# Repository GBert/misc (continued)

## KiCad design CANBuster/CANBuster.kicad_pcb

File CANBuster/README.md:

# MäCAN-Project

 by [Gerhard Bertelsmann](mailto:info@gerhard-bertelsmann.de) 

Hier entsteht ein System zur digitalen Steuerung einer Modellbahn, das auf dem CAN-Bus-Protokoll von Märklin basiert. Ziel ist es, eine preisgünstige und frei zugängliche Lösung zu schaffen.

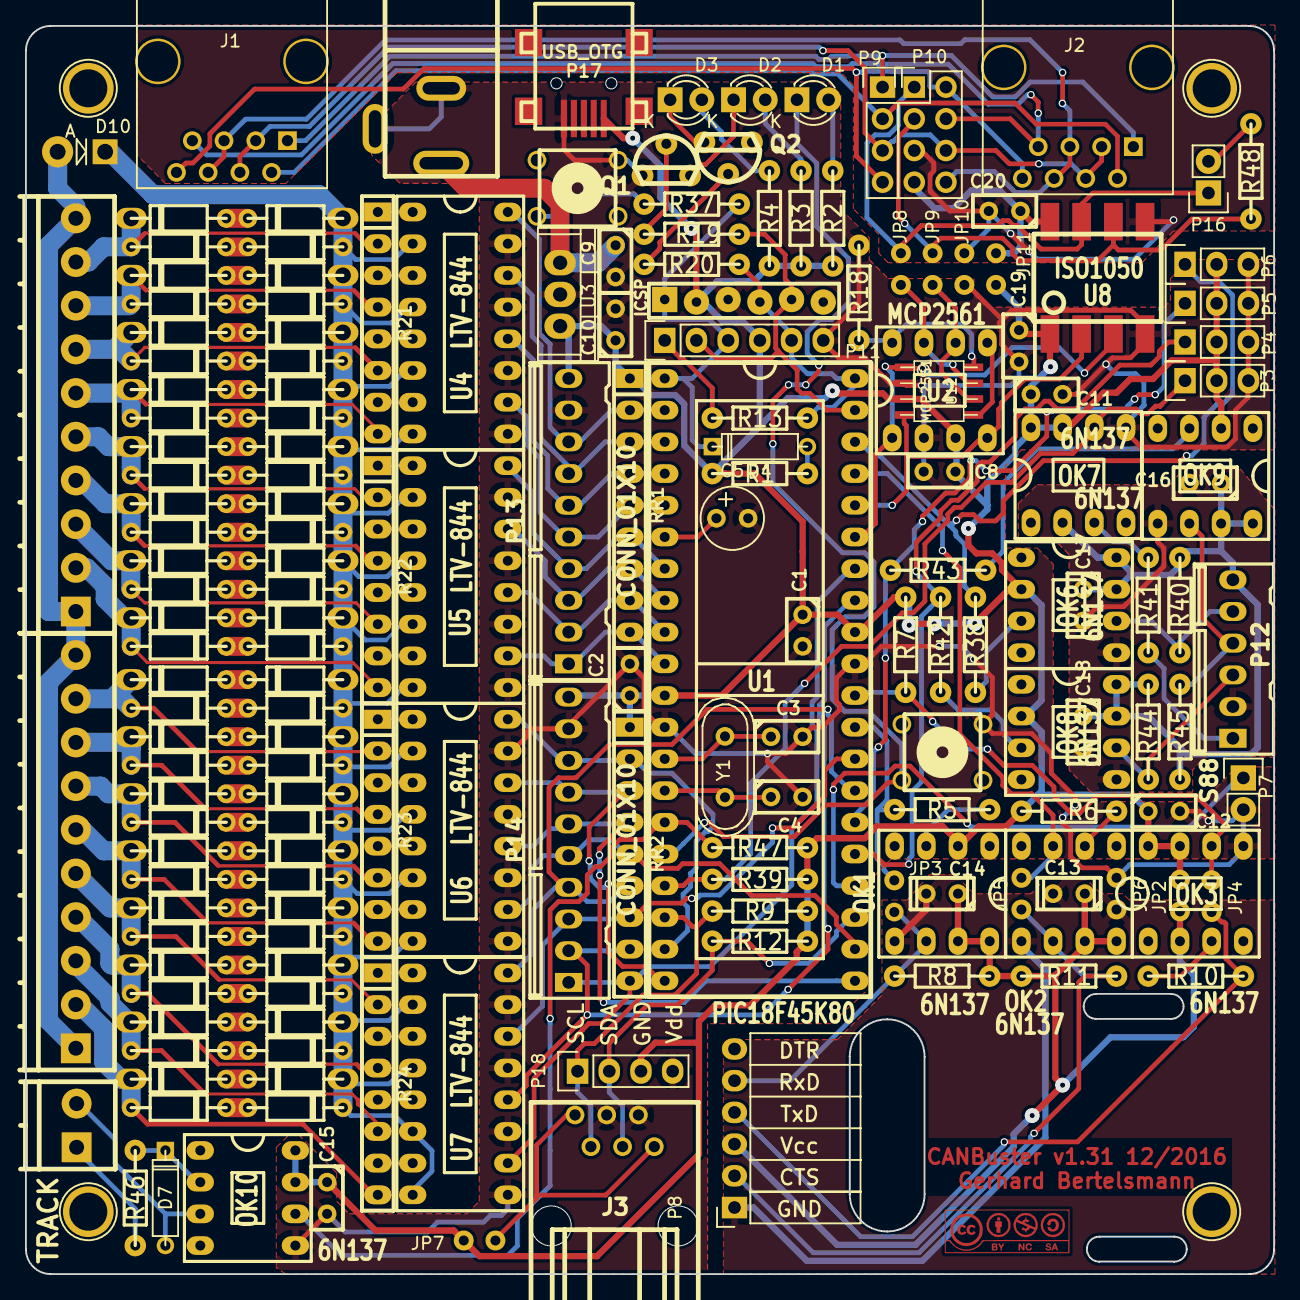
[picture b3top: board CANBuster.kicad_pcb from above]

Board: 2 copper layers, 100.0 x 100.0 mm, 177 parts (0 on the bottom side), 152 nets.

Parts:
C1, C2, C8, C9, C10, C11, C12, C13, C14, C15, C16, C17, C18, C19, C20: 100nF; cnp_3mm_disc
C3, C4: 22pf; cnp_3mm_disc
C5: 47uF; Elko_vert_11x5mm_RM2.5
CON1: BARREL_JACK; dc_socket
D1, D2, D3: LED; LED-3MM
D4: BAT43; D3
D7: 1N4148; D3
D10: D; Diode_DO-41_SOD81_Vertical_AnodeUp
D11, D12, D13, D14, D21, D22, D23, D24, D31, D32, D33, D34, D41, D42, D43, D44, D51, D52, D53, D54, D61, D62, D63, D64, D71, D72, D73, D74, D81, D82, D83, D84, D91, D92, D93, D94, D101, D102, D103, D104, D111, D112, D113, D114, D121, D122, D123, D124, D131, D132, D133, D134, D141, D142, D143, D144, D151, D152, D153, D154, D161, D162, D163, D164: D; diode_do35
J1, J2: RJ45; RJ45_8
J3: RJ12; molex_6p6c
JP1: ICSP
JP2, JP3, JP4, JP5, JP6, JP7, JP8, JP9, JP10, JP11: JUMPER; SolderWirePad_2x_0-2.54mmDrill
OK1, OK2, OK3, OK6, OK7, OK8, OK9, OK10: 6N137; dil_8-300_socket
P1, P2: CONN_01X10; pt_1,5-10-3,5-h
P3, P4, P5, P6: CONN_01X03; Pin_Header_Straight_1x03
P7, P16: CONN_01X02; Pin_Header_Straight_1x02
P8: CONN_01X06; Socket_Strip_Angled_1x06
P9, P18: CONN_01X04; Pin_Header_Straight_1x04
P10: CONN_02X04; Pin_Header_Straight_2x04
P11: RS232-Programmer; Socket_Strip_Straight_1x06
P12: S88; kk100_22-23-2061
P13, P14: CONN_01X10; kk100_22-23-2101
P15: TRACK; pt_1,5-2-3,5-h
P17: USB_OTG; conn_usb_B_mini_smd
Q1, Q2: BC547; to92_3
R1: 4k7; RC03
R2, R3, R4: 1,5k; RC03
R5, R6, R38, R41, R43, R47: 390; RC03
R7, R13, R39, R40, R44, R45: 1K; RC03
R8, R11: 1k; RC03
R9, R12: 3k3; RC03
R10: 270; RC03
R18, R19, R20: 10k; RC03
R21, R22, R23, R24: R-SIL_8NB; r-sil_8
R37: 470; RC03
R42: 330; RC03
R46: 1k5; RC03
R48: 120; RC03
RR1, RR2: RR8; r-sil_9
SW1, SW2: SW_PUSH; PCB_PUSH
U1: PIC18F45K80; dil_40-600_socket
U2: MCP2561; dil_8-300_socket
U3: 7805; TO-220
U4, U5, U6, U7: LTV-844; dil_16-300_socket
U8: ISO1050; mdip_8
U12: MCP2561; so-8
Y1: 16MHz; Crystal_HC49-U_Vertical

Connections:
+5V: C20.1, JP11.2, P10.7, U8.8
/CANH: JP8.2, P10.1, P16.1, U8.7
/CANL: JP9.2, P10.3, R48.1, U8.6
/CANRX: U1.36, U2.4, U8.2, U12.4
/CANTX: U1.35, U2.1, U8.3, U12.1
/CTS: JP5.1, OK2.3, U1.37
/IO1: P13.8, RR1.2, U1.2, U4.16
/IO2: P13.7, RR1.3, U1.3, U4.14
/IO3: P13.6, RR1.4, U1.4, U4.12
/IO4: P13.5, RR1.5, U1.5, U4.10
/IO5: P13.4, RR1.6, U1.7, U5.16
/IO6: P13.3, RR1.7, U1.8, U5.14
/IO7: P13.2, RR1.8, U1.9, U5.12
/IO8: P13.1, RR1.9, U1.10, U5.10
/IO9: P14.8, RR2.2, U1.19, U6.16
/IO10: P14.7, RR2.3, U1.20, U6.14
/IO11: P14.6, RR2.4, U1.21, U6.12
/IO12: P14.5, RR2.5, U1.22, U6.10
/IO13: P14.4, RR2.6, U1.27, U7.16
/IO14: P14.3, RR2.7, U1.28, U7.14
/IO15: P14.2, RR2.8, U1.33, U7.12
/IO16: P14.1, RR2.9, U1.34, U7.10
/PGC: JP1.5, P11.2, R19.2, U1.39
/PGD: JP1.4, P11.5, R13.1, R20.2, U1.40
/PGD_IN: P11.1, R13.2
/PWM1: OK7.6, P3.1, R39.1, U1.17
/PWM2: P4.1, R42.2, U1.25
/PWM3: P5.1, R43.2, U1.26
/PWM4: P6.1, R38.2, U1.38
/RxD: JP4.1, OK3.6, R7.1, U1.30
/S88_CLOCK: OK8.6, P12.3, R44.1
/S88_DATA: P12.1, R41.1
/S88_LOAD: OK9.6, P12.4, R45.1
/S88_RESET: OK6.6, P12.5, R40.1
/SCL: J3.2, P18.1, R9.1, U1.18
/SDA: J3.4, P18.2, R12.1, U1.23
/SNIFF: OK10.6, R47.1, U1.15
/STATUS: D1.1, SW2.2, U1.16
/TxD: JP3.1, R5.2, U1.29
/_CTS: JP5.2, OK2.6, P8.2, R11.2
/_RxD: JP3.2, OK1.6, P8.5, R8.1
/_TxD: JP4.2, P8.4, R10.1
/~MCLR: D4.1, JP1.1, P11.3, R37.1, U1.1
GND: C1.2, C2.2, C3.2, C4.2, C5.2, C8.2, C9.2, C10.2, C11.2, C12.2, C15.2, C19.2, CON1.1, CON1.2, J3.3, J3.5, JP1.3, JP6.1, JP10.1, OK3.5, OK7.5, OK10.5, P3.3, P4.3, P5.3, P6.3, P7.2, P11.6, P13.9, P14.9, P17.5, P18.4, Q1.3, Q2.3, R18.1, SW1.1, SW2.1, U1.12, U1.31, U2.2, U3.GND, U4.9, U4.11, U4.13, U4.15, U5.9, U5.11, U5.13, U5.15, U6.9, U6.11, U6.13, U6.15, U7.9, U7.11, U7.13, U7.15, U8.4, U12.2
GNDA: C16.2, C17.2, C18.2, OK6.5, OK8.5, OK9.5, P12.2
GNDD: C20.2, JP10.2, P10.5, U8.5
unnamed: C3.1, U1.13, Y1.1
unnamed: C4.1, U1.14, Y1.2
unnamed: C5.1, U1.6
unnamed: C9.1, CON1.3, U3.VI
unnamed: D1.2, R2.2
unnamed: D2.1, Q1.1
unnamed: D2.2, R3.2
unnamed: D3.1, Q2.1
unnamed: D3.2, R4.2
unnamed: D4.2, R1.2
unnamed: D7.1, OK10.2, R46.1
unnamed: D7.2, OK10.3, P15.2
unnamed: D10.1, D12.1, D14.2, D22.1, D24.2, D32.1, D34.2, D42.1, D44.2, D52.1, D54.2, D62.1, D64.2, D72.1, D74.2, D82.1, D84.2, D92.1, D94.2, D102.1, D104.2, D112.1, D114.2, D122.1, D124.2, D132.1, D134.2, D142.1, D144.2, D152.1, D154.2, D162.1, D164.2, U4.2, U4.4, U4.6, U4.8, U5.2, U5.4, U5.6, U5.8, U6.2, U6.4, U6.6, U6.8, U7.2, U7.4, U7.6, U7.8
unnamed: D10.2, P1.1, P1.10, P2.1, P2.10
unnamed: D11.1, D12.2
unnamed: D11.2, D13.1, P2.9, R21.2
unnamed: D13.2, D14.1
unnamed: D21.1, D22.2
unnamed: D21.2, D23.1, P2.8, R21.4
unnamed: D23.2, D24.1
unnamed: D31.1, D32.2
unnamed: D31.2, D33.1, P2.7, R21.6
unnamed: D33.2, D34.1
unnamed: D41.1, D42.2
unnamed: D41.2, D43.1, P2.6, R21.8
unnamed: D43.2, D44.1
unnamed: D51.1, D52.2
unnamed: D51.2, D53.1, P2.5, R22.2
unnamed: D53.2, D54.1
unnamed: D61.1, D62.2
unnamed: D61.2, D63.1, P2.4, R22.4
unnamed: D63.2, D64.1
unnamed: D71.1, D72.2
unnamed: D71.2, D73.1, P2.3, R22.6
unnamed: D73.2, D74.1
unnamed: D81.1, D82.2
unnamed: D81.2, D83.1, P2.2, R22.8
unnamed: D83.2, D84.1
unnamed: D91.1, D92.2
unnamed: D91.2, D93.1, P1.9, R23.2
unnamed: D93.2, D94.1
unnamed: D101.1, D102.2
unnamed: D101.2, D103.1, P1.8, R23.4
unnamed: D103.2, D104.1
unnamed: D111.1, D112.2
unnamed: D111.2, D113.1, P1.7, R23.6
unnamed: D113.2, D114.1
unnamed: D121.1, D122.2
unnamed: D121.2, D123.1, P1.6, R23.8
unnamed: D123.2, D124.1
unnamed: D131.1, D132.2
unnamed: D131.2, D133.1, P1.5, R24.2
unnamed: D133.2, D134.1
unnamed: D141.1, D142.2
unnamed: D141.2, D143.1, P1.4, R24.4
unnamed: D143.2, D144.1
unnamed: D151.1, D152.2
unnamed: D151.2, D153.1, P1.3, R24.6
unnamed: D153.2, D154.1
unnamed: D161.1, D162.2
unnamed: D161.2, D163.1, P1.2, R24.8
unnamed: D163.2, D164.1
unnamed: J1.1, J2.1, P9.1
unnamed: J1.2, J2.2, P9.2
unnamed: J1.3, J1.4, J2.3, J2.4, P9.3, P10.6
unnamed: J1.5, J1.6, J2.5, J2.6, P10.8
unnamed: J1.7, J2.7, P10.4
unnamed: J1.8, J2.8, P9.4, P10.2
unnamed: J3.1, J3.6, JP7.2
unnamed: JP8.1, U2.7, U12.7
unnamed: JP9.1, U2.6, U12.6
unnamed: OK1.3, R5.1
unnamed: OK2.2, R6.1
unnamed: OK3.3, R10.2
unnamed: OK6.3, R38.1
unnamed: OK7.3, R41.2
unnamed: OK8.3, R42.1
unnamed: OK9.3, R43.1
unnamed: P7.1, U1.24
unnamed: P15.1, R46.2
unnamed: P16.2, R48.2
unnamed: Q1.2, R19.1
unnamed: Q2.2, R20.1
unnamed: R18.2, U2.8, U12.8
unnamed: R21.1, U4.1
unnamed: R21.3, U4.3
unnamed: R21.5, U4.5
unnamed: R21.7, U4.7
unnamed: R22.1, U5.1
unnamed: R22.3, U5.3
unnamed: R22.5, U5.5
unnamed: R22.7, U5.7
unnamed: R23.1, U6.1
unnamed: R23.3, U6.3
unnamed: R23.5, U6.5
unnamed: R23.7, U6.7
unnamed: R24.1, U7.1
unnamed: R24.3, U7.3
unnamed: R24.5, U7.5
unnamed: R24.7, U7.7
unnamed: R37.2, SW1.2
unnamed: U2.5, U12.5
VCC: C16.1, C17.1, C18.1, OK6.7, OK6.8, OK7.2, OK8.7, OK8.8, OK9.7, OK9.8, P12.6, R40.2, R44.2, R45.2
VDD: C1.1, C2.1, C8.1, C10.1, C11.1, C12.1, C15.1, C19.1, JP1.2, JP2.1, JP7.1, JP11.1, OK1.2, OK3.7, OK3.8, OK6.2, OK7.7, OK7.8, OK8.2, OK9.2, OK10.7, OK10.8, P3.2, P4.2, P5.2, P6.2, P11.4, P13.10, P14.10, P17.1, P18.3, R1.1, R2.1, R3.1, R4.1, R6.2, R7.2, R9.2, R12.2, R39.2, R47.2, RR1.1, RR2.1, U1.11, U1.32, U2.3, U3.VO, U8.1, U12.3
VPP: C13.1, C14.1, JP2.2, OK1.7, OK1.8, OK2.7, OK2.8, OK3.2, P8.3, R8.2, R11.1
VSS: C13.2, C14.2, JP6.2, OK1.5, OK2.5, P8.1

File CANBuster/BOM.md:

Core
====
U1		PIC18F45K80 oder PIC18F46K80
U2 oder U12	MCP2561 DIL oder SMD
U3		LM7805
U4,U5,U6,U7	LTV-844
C1,C2		100nF RM2,5
C3,C4		22pF  RM2,5
C5		47uF  RM2,5
C8,C9,C10	100nF RM2,5
D1,D2		LED 3mm 2mA gelb
D3		LED 3mm 2mA rot
D4		BAT43
R1		4k7 Ohm
R2,R3,R4	1k5 Ohm
R13		1k Ohm
R18,R19,R20	10k Ohm
R37		390 Ohm
RR1,RR2		10k Ohm SIL 9-8
R21,R22,R23,R24	47 Ohm SIL 8-4
SW1,SW2		Mini-Taster
Q1,Q2		NPN Kleinsignaltransistor z.B. BC547 oder BC549
Y1 		16MHz Quarz HC49U-S
J1,J2		RJ45 Buchse MEBP 8-8S
P1,P2		Anschlussklemme 10 Pol 3,5 mm z.B. AKL059-10
P9		4 Pin Stiftleiste
P10		2x4 Pin Stiftleiste
P11,JP11	6 Pin Buchsenleiste
P13,P14		Printstecker PSS 254/10G
P15		Anschlussklemme 2 Pol 3,5 mm z.B. AKL059-02
P16		2 Pin Stiftleiste
SW1,SW2		Kurzhubtaster 6x6mm
D11..D162	noch nicht definiert

CAN Transceiver Option - galvanisch getrennte Option
----------------------------------------------------
U8		ISO1050 DUB(R)

I2C
===
R9,R12		3k3 Ohm
P18		Stiftleiste 3 Pin
J3		RJ12 Buchse MEBP 6-6S

PWM
===
P3,P4,P5,P6	Stiftleiste 3 Pin

S88
===
OK6,OK7,OK8,OK9	6N137
C11,C16,C17,C18	100nF RM2,5
R38,R41,R42,R43 390 Ohm
R39,R40,R44,R45 1k Ohm
P12		6 Pin Stiftleiste
2x Sockel	16 Pin		

Serielle Verbindung
===================
OK1,OK2,OK3	6N137
C13,C14		100nF RM2,5
R5,R6,R8,R11	390 Ohm
R7		1k Ohm
R10		270 Ohm
Sockel		8, 16 Pins
gewinkelte Buchsenleiste 6 Pol

Sniffer
=======
OK10		6N137
C15		100nF RM2,5
R46		1k5 Ohm
R47		390 Ohm
D7		1N4148

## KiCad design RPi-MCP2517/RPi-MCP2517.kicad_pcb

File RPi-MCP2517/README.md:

RPI-I2C/CAN Adapter with optional I2C Bus Extender
==================================================

```
# Determine RPi Version
cat /sys/firmware/devicetree/base/model
```

RPi2B Setup
----------
```
cd /tmp
wget "https://github.com/GBert/misc/raw/master/RPi-MCP2517/bin/mcp2517fd-rasp1+2+3.tar.gz"
cd / ; tar zxvf /tmp/mcp2517fd-rasp1+2+3.tar.gz

cat << EOF > /boot/config.txt
core_freq=250
kernel=ms7/zImage
device_tree=ms7/bcm2709-rpi-2-b.dtb
overlay_prefix=ms7/overlays/
dtoverlay=mcp2517fd-can0
dtparam=interrupt=25
dtparam=oscillator=4000000
dtparam=i2c_arm=on
EOF

reboot
```

RPi3 Setup
----------
```
cd /tmp
wget "https://github.com/GBert/misc/raw/master/RPi-MCP2517/bin/mcp2517fd-rasp1+2+3.tar.gz"
cd / ; tar zxvf /tmp/mcp2517fd-rasp1+2+3.tar.gz

cat << EOF > /boot/config.txt 
core_freq=250
kernel=ms7/zImage
device_tree=ms7/bcm2710-rpi-3-b.dtb
overlay_prefix=ms7/overlays/
dtoverlay=mcp2517fd-can0
dtparam=interrupt=25
dtparam=oscillator=4000000
dtparam=i2c_arm=on
EOF

reboot
```

Result
------
```
dmesg | egrep -i "can|spi" 
[    4.821482] CAN device driver interface
[    4.840982] mcp25xxfd spi0.0 can0: MCP2517 successfully initialized.
```

CAN Setup
---------
```
# setup 250kBaud
#  time quantum 250ns time quanta 16 => 16*250ns = 4us => 250kb
ip link set can0 up type can fd off tq 250 prop-seg 6 phase-seg1 7 phase-seg2 2 sjw 1 berr-reporting off restart-ms 100
ip -s -d link show can0
```

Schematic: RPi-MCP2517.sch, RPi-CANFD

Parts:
C1, C2: 22pF; C_0805_HandSoldering
C3, C4, C5, C6, C7, C8: 100nF; C_0805_HandSoldering
J1: Conn_01x06; Pin_Header_Angled_1x06_Pitch2.54mm
J2: Conn_01x02; Pin_Header_Straight_1x02_Pitch2.54mm
J3: DB9_Female_MountingHoles; DB_9M
P1: CONN_02X20; Socket_Strip_Straight_2x20
P2, P8: CONN_01X02; Pin_Header_Angled_1x02
P3, P4, P9: CONN_01X04; s4b-ph-kl
R1, R2, R3, R4: 4k7; R_0805_HandSolderingII
R5, R6, R8: 0; R_0805_HandSolderingII
R7: 120; R_1206_HandSolderingII
R9: 50; R_0805_HandSolderingII
R10, R11, R12, R13: 3k3; R_0805_HandSolderingII
U1: MCP2517FD; so-14
U2: MCP2562FD; so-8
U3: P82B715; so-8
U4: SI8641-SOIC; so-16
Y1: 4MHz; crystal_hc-49s

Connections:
+3V3: C3.1, C4.1, C6.1, C8.1, P1.1, P4.2, R1.1, R2.1, R3.1, R4.1, R10.1, R11.1, R12.1, R13.1, U1.14 (VDD), U2.5 (VIO~), U3.8 (VCC), U4.1
+5V: C5.1, P1.2, P3.2, P8.1, U2.3 (VDD~)
/CANH: J3.7, P3.3, R7.2, U2.7 (CANH)
/CANL: J3.2, P2.2, P3.4, U2.6 (CANL)
/CS0: P1.24, R2.2, U1.13 (nCS)
/GPIO4: P1.7, U4.6
/GPIO17: P1.11, U4.5
/GPIO22: P1.15, U4.3
/GPIO27: P1.13, U4.4
/INT: P1.22, R1.2, U1.4 (/INT)
/INT0: R5.2, U1.9 (/INT0)
/INT0_: P1.16, R3.2, R5.1
/INT1: R6.2, U1.8 (/INT1)
/INT1_: P1.18, R4.2, R6.1
/MISO: P1.21, U1.12 (SDO)
/MOSI: P1.19, U1.11 (SDI)
/RxD: P1.10, P4.4
/SCK: P1.23, U1.10 (SCK)
/SCL: P1.5, R11.2, U3.3 (SX)
/SDA: P1.3, R10.2, U3.6 (SY)
/TxD: P1.8, P4.3
GND: C1.2, C2.2, C3.2, C4.2, C5.2, C6.2, C8.2, J3.3, J3.6, P1.6, P1.9, P3.1, P4.1, P9.1, U1.7 (VSS), U2.2 (VSS~), U2.8 (STBY), U3.4 (GND), U4.2, U4.8
GNDA: C7.2, J1.5, J2.2, U4.9, U4.15
unnamed: C1.1, U1.5 (OSC2), Y1.1
unnamed: C2.1, U1.6 (OSC1), Y1.2
unnamed: J1.2, U4.14
unnamed: J1.3, U4.13
unnamed: J1.4, R8.2
unnamed: J1.6, R9.2
unnamed: P2.1, R7.1
unnamed: P8.2, P9.2
unnamed: P9.3, R13.2, U3.7 (LY)
unnamed: P9.4, R12.2, U3.2 (LX)
unnamed: R8.1, U4.12
unnamed: R9.1, U4.11
unnamed: U1.1 (TXCAN), U2.1 (TXD)
unnamed: U1.2 (RXCAN), U2.4 (RXD)
VDDA: C7.1, J1.1, J2.1, U4.16

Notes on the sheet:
I2C Option
UART Option
GPIO Option

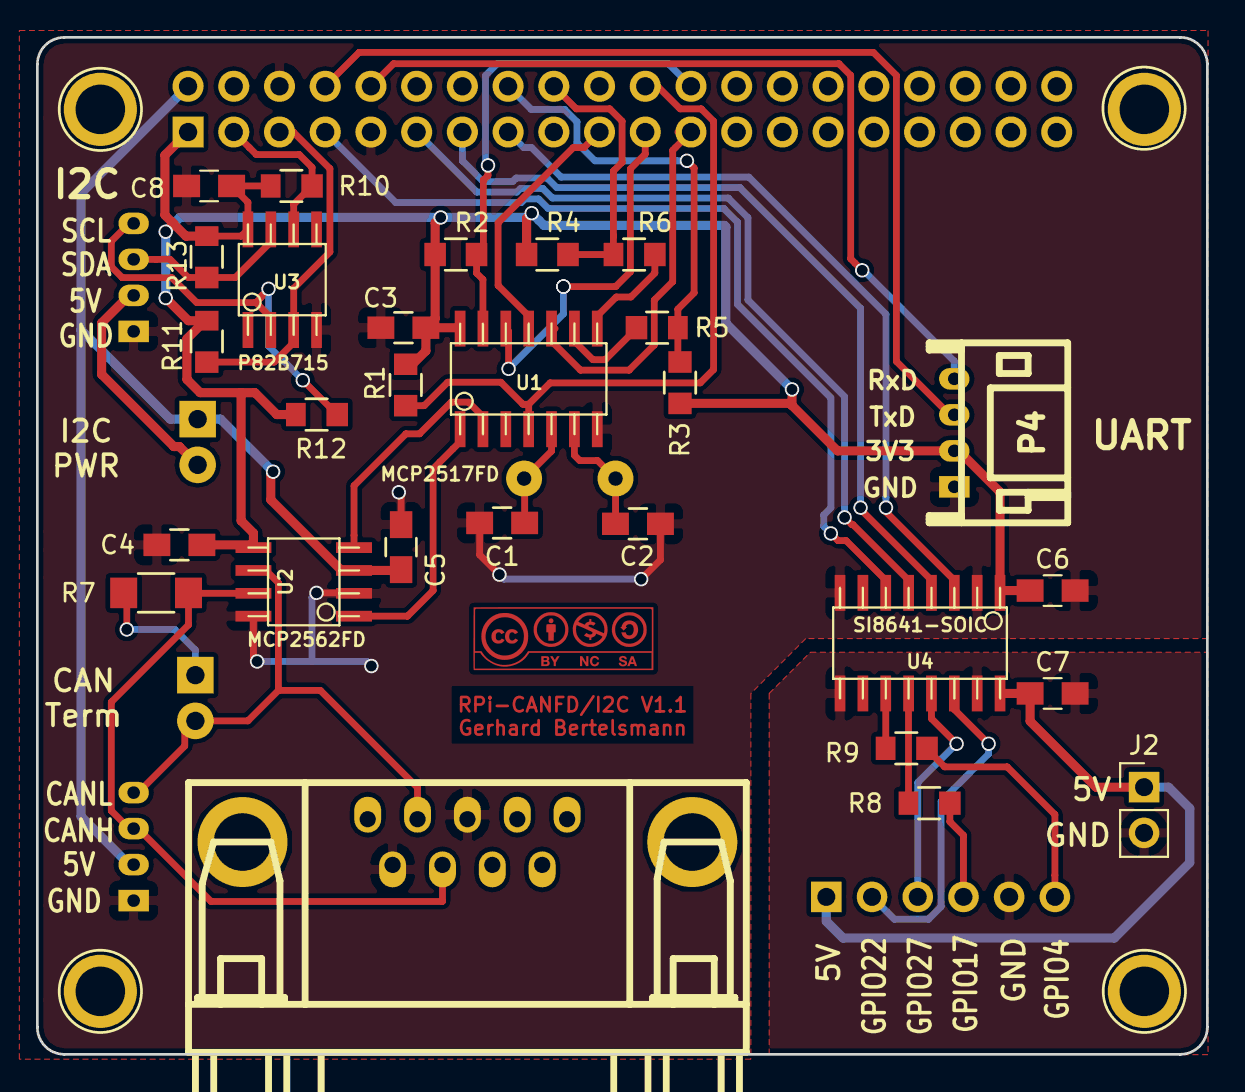
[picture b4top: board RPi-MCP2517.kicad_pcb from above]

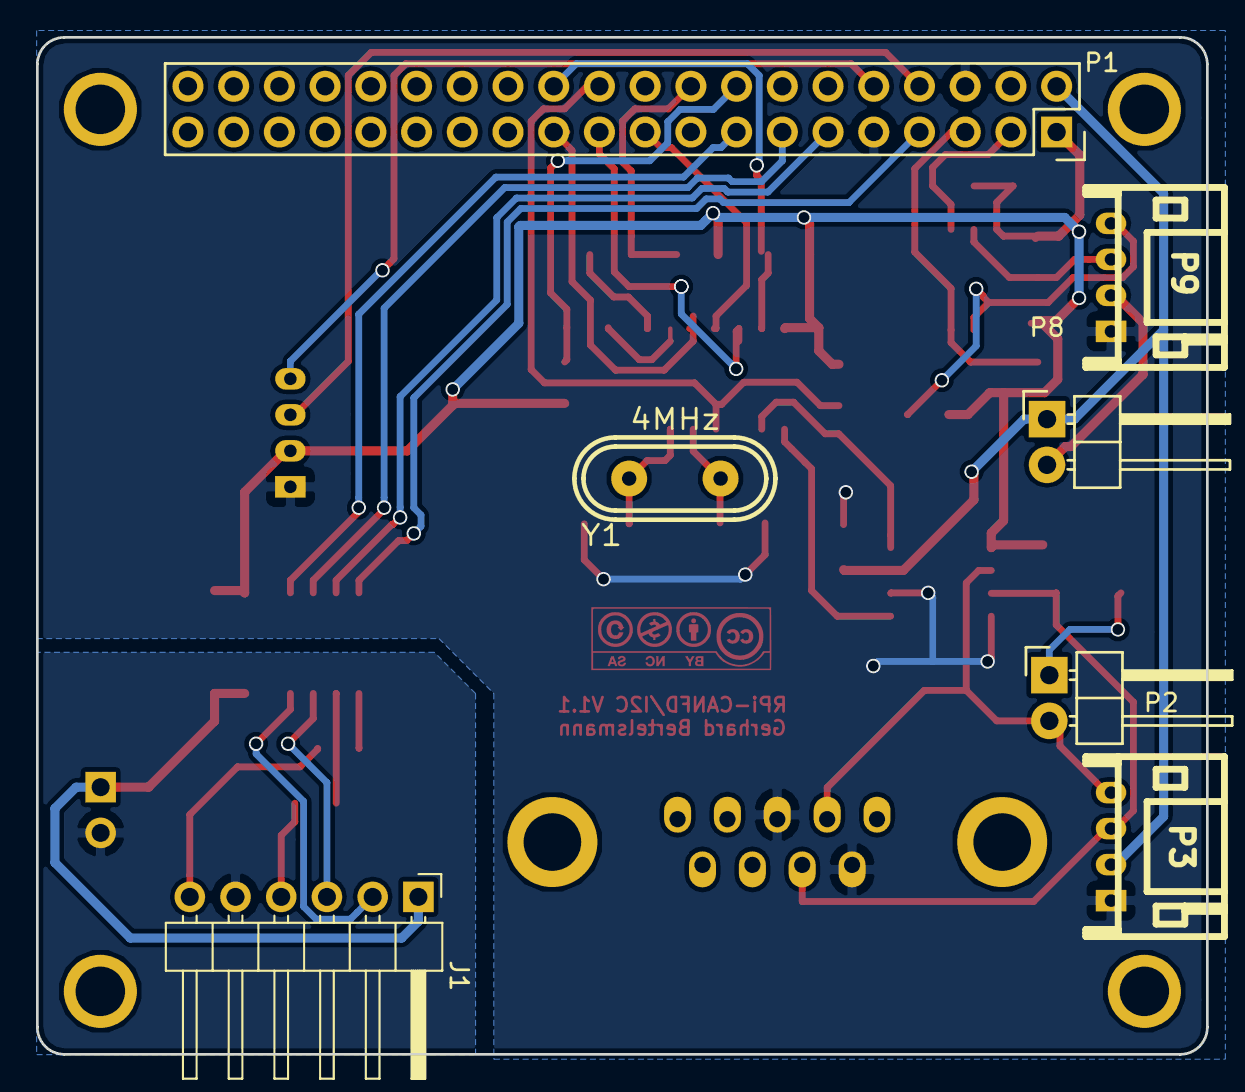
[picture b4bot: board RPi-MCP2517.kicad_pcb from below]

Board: 2 copper layers, 65.0 x 56.5 mm, 35 parts (7 on the bottom side), 38 nets.

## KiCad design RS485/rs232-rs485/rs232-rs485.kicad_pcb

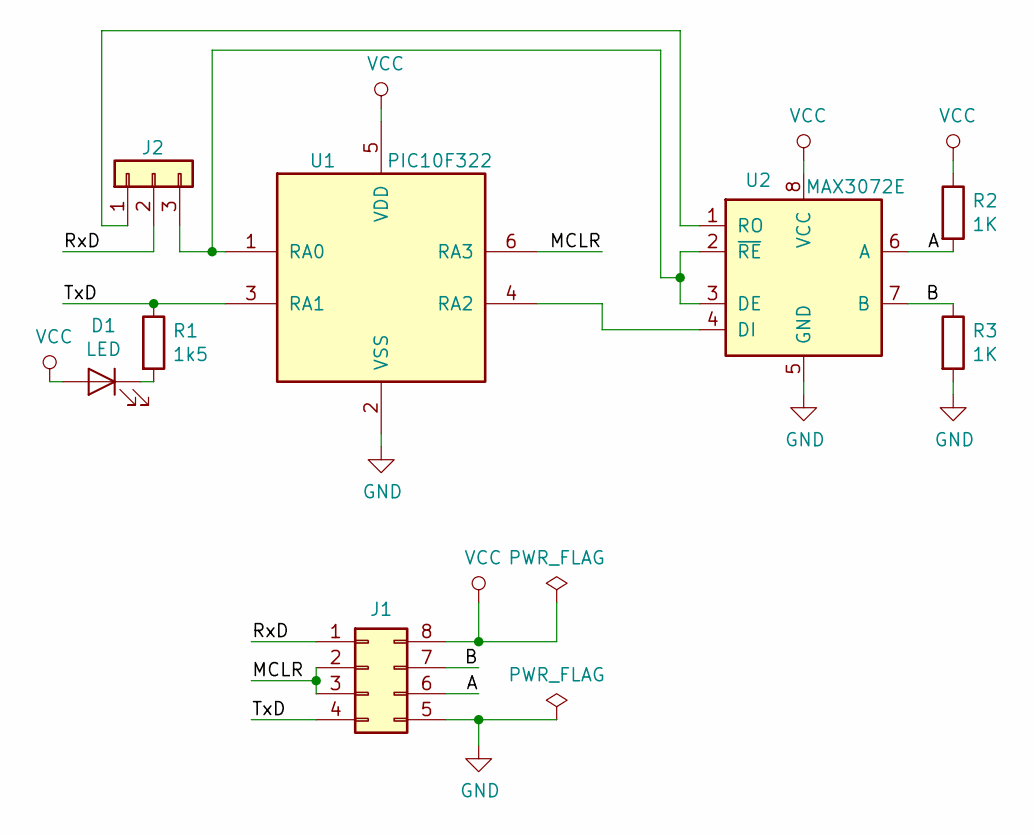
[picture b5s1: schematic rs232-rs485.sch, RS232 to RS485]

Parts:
D1: LED; LED_0805_2012Metric
J1: Conn_02x04_Counter_Clockwise; DIP-8_W7.62mm_Socket
J2: Conn_01x03; PinHeader_1x03_P2.00mm_Vertical
R1: 1k5; R_0805_2012Metric
R2, R3: 1K; R_0805_2012Metric
U1: PIC10F322; SOT-23-6
U2: MAX3072E; SOIC-8_3.9x4.9mm_P1.27mm

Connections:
/A: J1.6, R2.2, U2.6 (A)
/B: J1.7, R3.1, U2.7 (B)
/MCLR: J1.2, J1.3, U1.6 (RA3)
/RxD: J1.1, J2.2
/TxD: J1.4, R1.1, U1.3 (RA1)
GND: J1.5, R3.2, U1.2 (VSS), U2.5 (GND)
unnamed: D1.1 (K), R1.2
unnamed: J2.1, U2.1 (RO)
unnamed: J2.3, U1.1 (RA0), U2.2 (~RE~), U2.3 (DE)
unnamed: U1.4 (RA2), U2.4 (DI)
VCC: D1.2 (A), J1.8, R2.1, U1.5 (VDD), U2.8 (VCC)

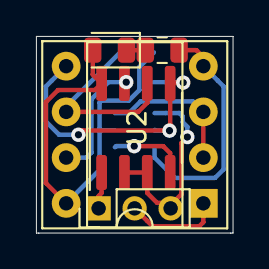
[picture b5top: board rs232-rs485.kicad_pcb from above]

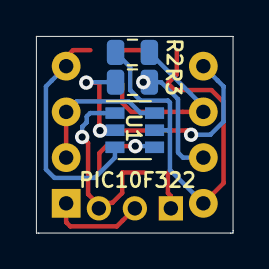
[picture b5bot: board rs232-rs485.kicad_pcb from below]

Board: 2 copper layers, 10.9 x 10.9 mm, 8 parts (3 on the bottom side), 11 nets.

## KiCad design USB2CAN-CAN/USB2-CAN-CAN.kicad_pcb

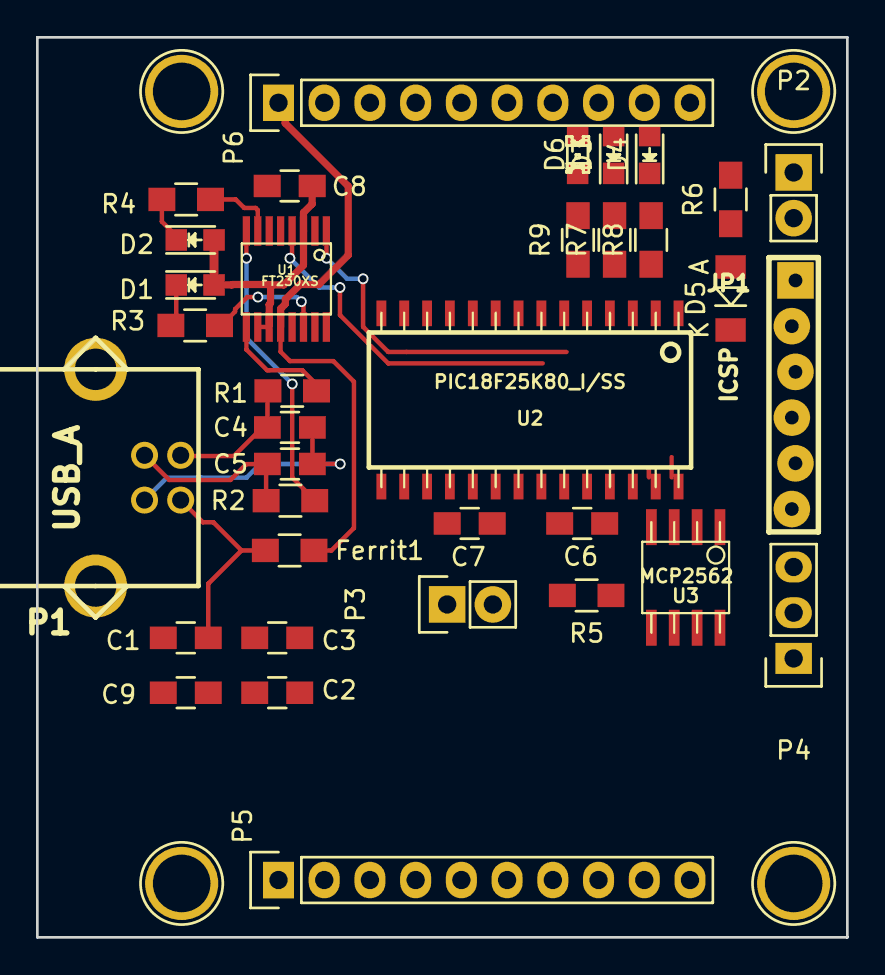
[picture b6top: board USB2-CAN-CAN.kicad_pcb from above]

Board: 2 copper layers, 45.0 x 50.0 mm, 39 parts (0 on the bottom side), 47 nets.

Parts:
C1: 10nf; C_0805_HandSoldering
C2, C4: 47pF; C_0805_HandSoldering
C3, C5: 47pf; C_0805_HandSoldering
C6, C7, C8: 100nF; C_0805_HandSoldering
C9: CP; C_0805_HandSoldering
D1, D2, D3, D4, D6: LED; LED-0805
D5: BAT43; MiniMELF_Standard
Ferrit1: 10uH; R_0805_HandSoldering
HLD: 1pin
HLU: 1pin
HRD: 1pin
HRU: 1pin
JP1: ICSP
P1: USB_A; conn_usb_B
P2: Prog; Pin_Header_Straight_1x02
P3: Term; Pin_Header_Straight_1x02
P4: CONN_01X03; Pin_Header_Straight_1x03
P5: CON1; Pin_Header_Straight_1x10
P6: CON2; Pin_Header_Straight_1x10
R1, R2: 27; R_0805_HandSoldering
R3, R4, R7, R8, R9: 270; R_0805_HandSoldering
R5: 120; R_0805_HandSoldering
R6: 4k7; R_0805_HandSoldering
U1: FT230XS; ssop-16
U2: PIC18F25K80_I/SS; soic-28
U3: MCP2562; so-8

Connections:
//MCLR: D5.1, JP1.1, P2.2, U2.1
/CANRX: P5.6, U2.24, U3.4
/CANTX: P5.5, U2.23, U3.1
/CLKOUT: P5.10, U2.10
/PGC: JP1.5, U1.4, U2.27
/PGD: JP1.4, U1.1, U2.28
/RA3: R9.1, U2.5
/RA5: P5.9, U2.7
/RB0: P5.3, U2.21
/RB1: P5.4, U2.22
/RB4: P5.7, U2.25
/RB5: P5.8, U2.26
/RC0: P6.3, U2.11
/RC1: P6.4, U2.12
/RC2: P6.5, U2.13
/RC3: P6.6, U2.14
/RC4: P6.7, U2.15
/RC5: P6.8, U2.16
/RC6: P6.9, U2.17
/RC7: P6.10, U2.18
GND: C1.2, C4.2, C5.2, C6.2, C7.2, C8.2, C9.2, JP1.3, P1.4, P4.3, P5.2, P6.2, U1.5, U1.13, U2.8, U2.19, U3.2, U3.8
unnamed: C1.1, Ferrit1.2, P1.1
unnamed: C2.1, C3.1
unnamed: C2.2, C3.2
unnamed: C4.1, P1.2, R1.2
unnamed: C5.1, P1.3, R2.2
unnamed: C9.1, U2.6
unnamed: D1.1, R3.2
unnamed: D2.1, R4.2
unnamed: D3.1, R7.2
unnamed: D4.1, R8.2
unnamed: D5.2, R6.1
unnamed: D6.1, R9.2
unnamed: P2.1, U1.2
unnamed: P3.1, R5.2
unnamed: P3.2, P4.2, U3.6
unnamed: P4.1, R5.1, U3.7
unnamed: R1.1, U1.9
unnamed: R2.1, U1.8
unnamed: R3.1, U1.14
unnamed: R4.1, U1.7
unnamed: R7.1, U2.4
unnamed: R8.1, U2.3
unnamed: U1.6, U2.2
unnamed: U1.16, U2.9
VCC: Ferrit1.1, P6.1, U1.12, U3.3
VCOM: C6.1, C7.1, C8.1, D1.2, D2.2, D3.2, D4.2, D6.2, P5.1, R6.2, U1.3, U1.10, U1.11, U3.5

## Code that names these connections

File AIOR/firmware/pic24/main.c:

/* ----------------------------------------------------------------------------
 * "THE BEER-WARE LICENSE" (Revision 42):
 * <info@gerhard-bertelsmann.de> wrote this file. As long as you retain this
 * notice you can do whatever you want with this stuff. If we meet some day,
 * and you think this stuff is worth it, you can buy me a beer in return
 * Gerhard Bertelsmann
 * ----------------------------------------------------------------------------
 */

#include "main.h"
#include "can.h"

#pragma config JTAGEN   = OFF
#pragma config FNOSC    = PRIPLL
#pragma config IESO     = OFF
#pragma config FCKSM    = CSECMD
#pragma config OSCIOFNC = ON
#pragma config POSCMD   = XT
#pragma config FWDTEN   = OFF

volatile uint16_t LED_Counter = 0;
volatile uint16_t tcounter = 0;

/* code for Timer1 ISR*/
void __attribute__((__interrupt__, no_auto_psv)) _T1Interrupt(void) {
    /* Clear OC1 interrupt flag} */
    IFS0bits.T1IF = 0;
    LED_Counter++;
    if (LED_Counter >= 500) {
	//__builtin_btg((unsigned int *)&LATB, 9);
	LED_Counter = 0;
    }
}

/* code for Timer2 ISR*/
void __attribute__((__interrupt__, no_auto_psv)) _T2Interrupt(void) {
    IFS0bits.T2IF = 0;
}

/* code for Timer9 ISR */
void __attribute__((__interrupt__, no_auto_psv)) _T9Interrupt(void) {
    IFS3bits.T9IF = 0;
    tcounter++;
}

/* code for Output Compare 1 ISR*/
void __attribute__((__interrupt__, no_auto_psv)) _OC1Interrupt(void) {
    /* Clear OC1 interrupt flag} */
    IFS0bits.OC1IF = 0;
}

/* code for Output Compare 2 ISR*/
void __attribute__((__interrupt__, no_auto_psv)) _OC2Interrupt(void) {
    /* Clear OC2 interrupt flag} */
    IFS0bits.OC2IF = 0;
}

void init_timer(void) {
    /* Timer1 for msic tasks */
    T1CONbits.TON = 0;        // Disable Timer
    T1CONbits.TCS = 0;        // Select internal instruction cycle clock
    T1CONbits.TGATE = 0;      // Disable Gated Timer mode
    T1CONbits.TCKPS = 0b10;   // Select 1:64 Prescaler
    TMR1 = 0x0000;            // Clear timer register
    PR1 = 999;                // Load the period value / 64MHz / 64 *1000 -> 1ms
    IPC0bits.T1IP = 0x01;     // Set Timer1 Interrupt Priority Level
    IFS0bits.T1IF = 0;        // Clear Timer1 Interrupt Flag
    IEC0bits.T1IE = 1;        // Enable Timer1 interrupt
    T1CONbits.TON = 1;        // Start Timer

    /* Timer2 for Output Compare - 1 tick = 1us */
    T2CONbits.TON = 0;        // Disable Timer
    T2CONbits.TCS = 0;        // Select internal instruction cycle clock
    T2CONbits.TGATE = 0;      // Disable Gated Timer mode
    T2CONbits.TCKPS = 0b10;   // Select 1:64 Prescaler
    TMR2 = 0x0000;            // Clear timer register
    PR2 = 99;             // Load the period value
    IFS0bits.T2IF = 0;        // Clear Timer1 Interrupt Flag
    IEC0bits.T2IE = 0;        // Disable Timer1 interrupt
    // T2CONbits.TON = 1;        // Start Timer TODO

    /* Timer8&9 32 Bit free running counter - 1 tick = 1us */
    T9CONbits.TON = 0;        // Stop any 16-bit Timer9 operation
    T8CONbits.TON = 0;        // Stop any 16/32-bit Timer8 operation
    T8CONbits.T32 = 1;        // Enable 32-bit Timer mode
    T8CONbits.TCS = 0;        // Select internal instruction cycle clock
    T8CONbits.TGATE = 0;      // Disable Gated Timer mode
    T8CONbits.TCKPS = 0b10;   // Select 1:64 Prescaler
    TMR9 = 0x0000;            // Clear 32-bit Timer (msw)
    TMR8 = 0x0000;            // Clear 32-bit Timer (lsw)
    PR9 = 0xffff;             // Load 32-bit period value (msw)
    PR8 = 0xffff;             // Load 32-bit period value (lsw)
    IPC13bits.T9IP = 0x01;    // Set Timer9 Interrupt Priority Level
    IFS3bits.T9IF = 0;        // Clear Timer9 Interrupt Flag
    IEC3bits.T9IE = 1;        // Enable Timer9 interrupt
    T8CONbits.TON = 1;        // Start 32-bit Time

    /* Prepare Output Compare 1 for track signal using default Timer2 */
    OC1CON1         = 0x0000;     // Turn off Output Compare 1 Module
    //OC1CON1         = 0x0004;     // Load new compare mode to OC1CON                      TODO
    OC1CON1         = 0x0005;     // Load new compare mode to OC1CON                      TODO
    OC1R            = 4;         // Initialize Compare Register1 with 5             TODO
    OC1RS           = 44;         // Initialize Secondary Compare Register1 with 45   TODO
    IPC0bits.OC1IP0 = 1;          // Setup Output Compare 1 interrupt for
    IPC0bits.OC1IP1 = 0;          // desired priority level
    IPC0bits.OC1IP2 = 0;
    IFS0bits.OC1IF  = 0;          // Clear Output Compare 1 interrupt flag
    IEC0bits.OC1IE  = 1;          // Enable Output Compare 1 interrupt

    /* Prepare Output Compare 2 for track signal using default Timer2 */
    OC2CON1         = 0x0000;     // Turn off Output Compare 1 Module
    //OC2CON1         = 0x0004;     // Load new compare mode to OC1CON                      TODO
    OC2CON1         = 0x0005;     // Load new compare mode to OC1CON                      TODO
    OC2R            = 54;    // Initialize Compare Register1 with 0x3000             TODO
    OC2RS           = 94;     // Initialize Secondary Compare Register1 with 0x3003   TODO
    IPC1bits.OC2IP0 = 1;          // Setup Output Compare 1 interrupt for
    IPC1bits.OC2IP1 = 0;          // desired priority level
    IPC1bits.OC2IP2 = 0;
    IFS0bits.OC2IF  = 0;          // Clear Output Compare 1 interrupt flag
    IEC0bits.OC2IE  = 1;          // Enable Output Compare 1 interrupt

    T2CONbits.TON = 1;        // Start Timer TODO
}

void init_io(void) {
    /* ADC1 Digital Mode */
    // AD1CON1.bits = 0x8000;
    //_ADON = 0;
    //_CVR1OE = 0;
    CM1CON = 0;
    CM2CON = 0;
    CM3CON = 0;
    CM5CON = 0;
    ANSELA = 0;
    ANSELB = 0;
    ANSELC = 0;
    // AD1PCFG = 0xFFFF;
    /* RB9 LED */
    TRISB = 0;
    //TRISC = 0x0080;
    LATCbits.LATC6 = 1;
    TRISCbits.TRISC6 = 0;
    TRISCbits.TRISC7 = 1;
    LATCbits.LATC9 = 1;
    TRISCbits.TRISC8 = 1;
    TRISCbits.TRISC9 = 0;
}

void init_pps(void) {
    __builtin_write_OSCCONL(OSCCON & ~(1 << 6));
    RPINR18bits.U1RXR = 34;     /* PIN 23 RB2 RPI34 U1RxD */
    RPOR0bits.RP35R   =  1;     /* PIN 22 RB3 RP35  U1TxD (U1TX = 0b0000001) */
    RPINR26bits.C1RXR = 55;     /* PIN 3  RC7 RP55 CAN1 RxD */
    RPOR6bits.RP54R   = 14;     /* PIN 2  RC6 RP54 CAN1 TxD (C1TX = 0b001110) */
    RPINR19bits.U2RXR = 42;     /* PIN 8  RB10 RP42 U2RxD */
    RPOR4bits.RP42R   =  3;     /* PIN 9  RB11 RP43 U2TxD (U2TX = 0b0000011) */
    RPOR2bits.RP39R   = 16;     /* PIN 43 RB7  RP39 B_Left  (OC1 = 0b00010000) */
    RPOR3bits.RP40R   = 17;     /* PIN 44 RB8  RP40 B_Right (OC2 = 0b00010001) */
                                /* PIN 42 RB6  RP38 B_Ena */
    __builtin_write_OSCCONL(OSCCON | (1 << 6));
}

int main(void) {
    /* Init Clock */
    PLLFBD = PLL_DIV;
    CLKDIVbits.PLLPOST = PLL_POST;
    CLKDIVbits.PLLPRE = PLL_PRE;

    __builtin_write_OSCCONH(0x03);
    __builtin_write_OSCCONL(OSCCON | 0x01);

    while (OSCCONbits.COSC != 3) ;
    while (OSCCONbits.LOCK != 1) ;

    init_io();
    init_pps();
    init_timer();
    init_can();

    while (true) {
	__delay_ms(500);
	__builtin_btg((unsigned int *)&LATB, 9);
	can_test_send();
	ClrWdt();
    }
}
